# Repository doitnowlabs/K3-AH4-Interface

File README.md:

K3-AH4-Interface
================

A project that enables the use of the Icom AH4 autotuner with the Elecraft K3 and KX3 radios.

Edit -- March 2021: Greetings from the future! Many people have got in contact with me or my Dad asking for more information about this project over the ~7 years since it was created (if you contacted me and I didn't see the message/did not respond, I apologize!). Although it's a little late, I'm uploading all the files I have relating to the k3-ah4 interface so hopefully others can reproduce it without needing to rely on me checking my GitHub messages infrequently.

One note is that this project switches RS232 lines in and out of circuit with an analog switch, which definitely does not comply with the RS232 standard. The project worked great in the state I'm uploading it in, but it wouldn't pass a compliance test. As with all my work, use at your own risk, and have fun!

Schem. and board files are Eagle format. There's a free version of Eagle available to download if you don't own a copy already.

Ben

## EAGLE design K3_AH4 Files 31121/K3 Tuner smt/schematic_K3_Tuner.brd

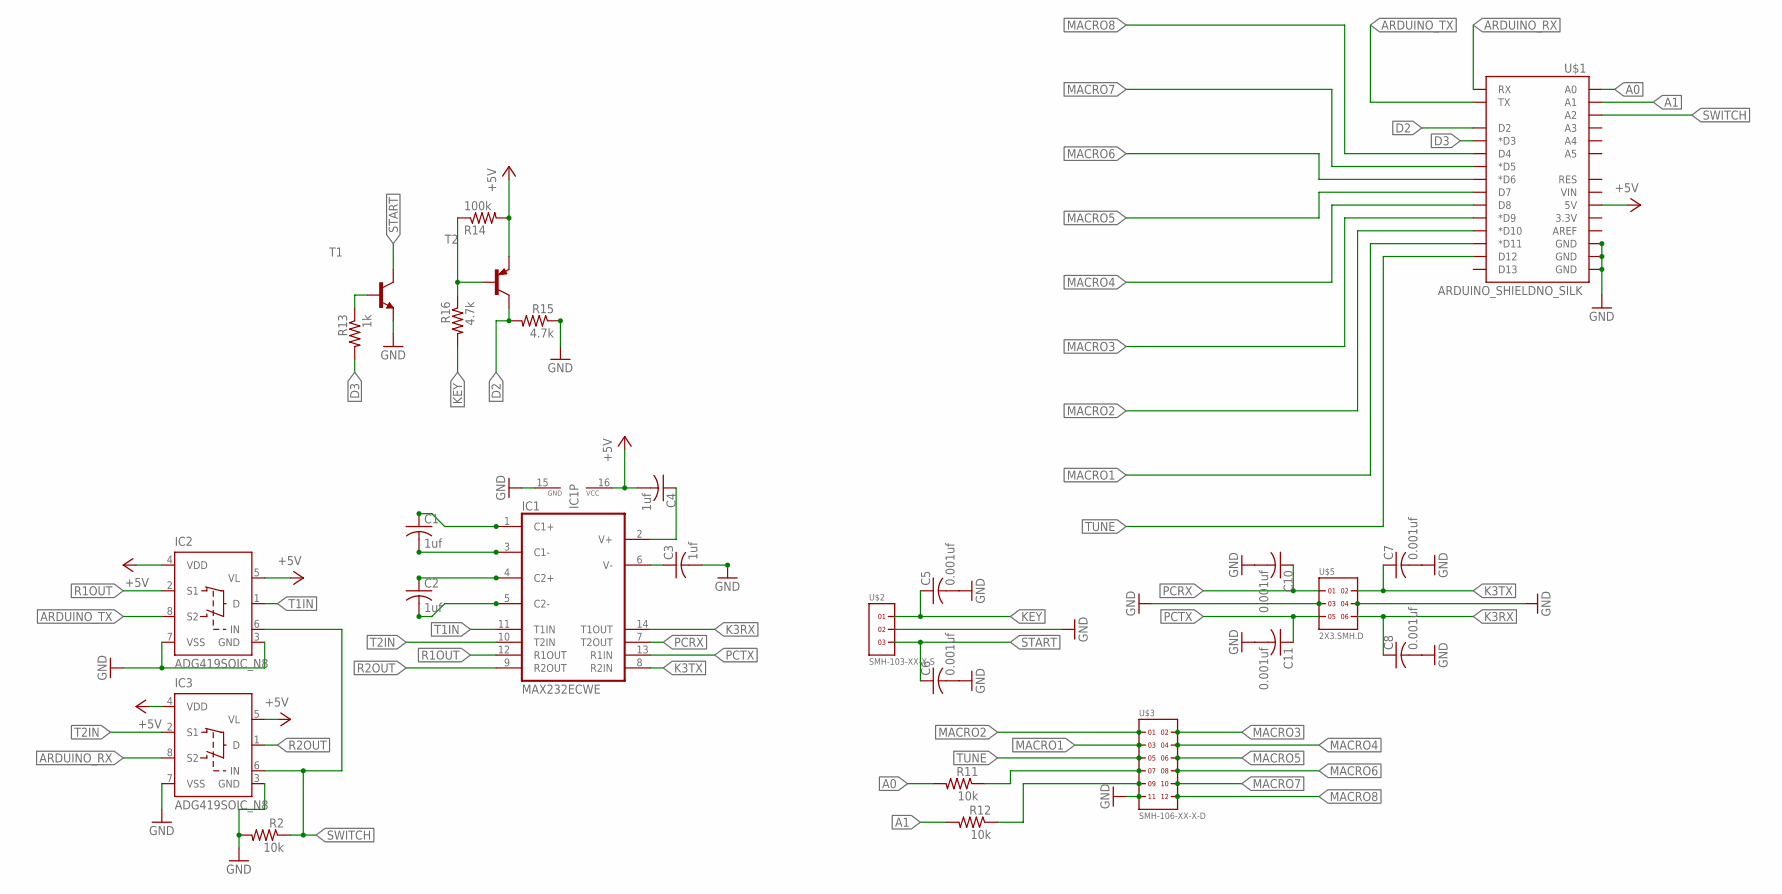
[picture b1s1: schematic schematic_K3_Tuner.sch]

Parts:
C1, C2, C3, C4: 1uf; C0805
C5, C6, C7, C8, C10, C11: 0.001uf; C0805
IC1: MAX232ECWE; SO16L
IC2, IC3: ADG419SOIC_N8; SOIC8
R2, R11, R12: 10k; M0805
R13: 1k; M0805
R14: 100k; M0805
R15, R16: 4.7k; M0805
T1: MMBT3904LT1-NPN-SOT23-BEC; SOT23-BEC
T2: MMBT3906LT1-PNP-SOT23-BEC; SOT23-BEC
U$1: ARDUINO_SHIELDNO_SILK; DUEMILANOVE_VIAS
U$2: SMH-103-XX-X-S
U$3: SMH-106-XX-X-D
U$5: 2X3.SMH.D; SMH-103-XX-X-D

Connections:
+5V: C4.2, IC1.16 (VCC), IC2.4 (VDD), IC2.5 (VL), IC3.4 (VDD), IC3.5 (VL), R14.2, T2.E, U$1.5V
A0: R11.2, U$1.A0
A1: R12.2, U$1.A1
ARDUINO_RX: IC3.8 (S2), U$1.RX
ARDUINO_TX: IC2.8 (S2), U$1.TX
D2: R15.2, T2.C, U$1.D2
D3: R13.2, U$1.D3 (*D3)
GND: C3.2, C5.2, C6.2, C7.2, C8.2, C10.2, C11.2, IC1.15 (GND), IC2.3 (GND), IC2.7 (VSS), IC3.3 (GND), IC3.7 (VSS), R2.2, R15.1, T1.E, U$1.GND@0 (GND), U$1.GND@1 (GND), U$1.GND@2 (GND), U$2.2, U$3.11, U$5.3, U$5.4
K3RX: C8.1, IC1.14 (T1OUT), U$5.6
K3TX: C7.1, IC1.8 (R2IN), U$5.2
KEY: C5.1, R16.2, U$2.1
MACRO1: U$1.D11 (*D11), U$3.3
MACRO2: U$1.D10 (*D10), U$3.1
MACRO3: U$1.D9 (*D9), U$3.2
MACRO4: U$1.D8, U$3.4
MACRO5: U$1.D7, U$3.6
MACRO6: U$1.D6 (*D6), U$3.8
MACRO7: U$1.D5 (*D5), U$3.10
MACRO8: U$1.D4, U$3.12
unnamed: R11.1, U$3.7
unnamed: R12.1, U$3.9
unnamed: C2.2, IC1.5 (C2-)
unnamed: C2.1, IC1.4 (C2+)
unnamed: C1.2, IC1.3 (C1-)
unnamed: C1.1, IC1.1 (C1+)
unnamed: C3.1, IC1.6 (V-)
unnamed: R13.1, T1.B
unnamed: R14.1, R16.1, T2.B
unnamed: C4.1, IC1.2 (V+)
PCRX: C10.1, IC1.7 (T2OUT), U$5.1
PCTX: C11.1, IC1.13 (R1IN), U$5.5
R1OUT: IC1.12 (R1OUT), IC2.2 (S1)
R2OUT: IC1.9 (R2OUT), IC3.1 (D)
START: C6.1, T1.C, U$2.3
SWITCH: IC2.6 (IN), IC3.6 (IN), R2.1, U$1.A2
T1IN: IC1.11 (T1IN), IC2.1 (D)
T2IN: IC1.10 (T2IN), IC3.2 (S1)
TUNE: U$1.D12, U$3.5

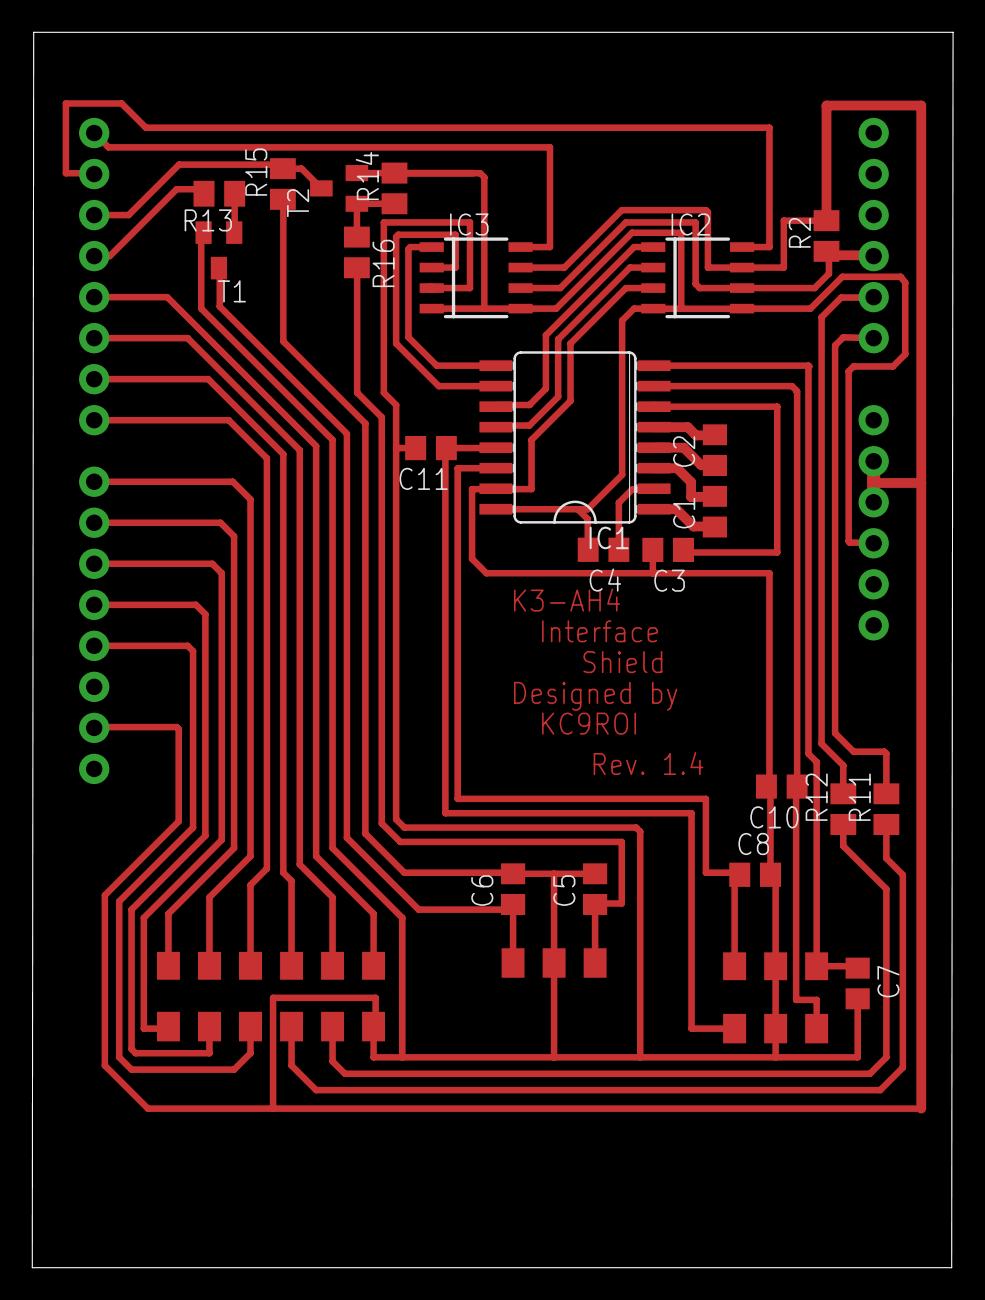
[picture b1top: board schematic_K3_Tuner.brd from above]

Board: 2 copper layers, 57.0 x 76.5 mm, 26 parts (0 on the bottom side), 38 nets.

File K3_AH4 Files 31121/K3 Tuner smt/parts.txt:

Partlist

Exported from schematic_K3_Tuner.sch at 3/28/2014 2:09:03 AM

EAGLE Version 6.5.0 Copyright (c) 1988-2013 CadSoft

Assembly variant: 

Part     Value                 Device                    Package          Library          Sheet

C1       1uf                   C-USC0805                 C0805            rcl              1
C2       1uf                   C-USC0805                 C0805            rcl              1
C3       1uf                   C-USC0805                 C0805            rcl              1
C4       1uf                   C-USC0805                 C0805            rcl              1
C5       0.001uf               C-USC0805                 C0805            rcl              1
C6       0.001uf               C-USC0805                 C0805            rcl              1
C7       0.001uf               C-USC0805                 C0805            rcl              1
C8       0.001uf               C-USC0805                 C0805            rcl              1
C10      0.001uf               C-USC0805                 C0805            rcl              1
C11      0.001uf               C-USC0805                 C0805            rcl              1
IC1      MAX232ECWE            MAX232ECWE                SO16L            maxim            1
IC2      ADG419SOIC_N8         ADG419SOIC_N8             SOIC8            K3Library        1
IC3      ADG419SOIC_N8         ADG419SOIC_N8             SOIC8            K3Library        1
R2       10k                   R-US_M0805                M0805            resistor         1
R11      10k                   R-US_M0805                M0805            resistor         1
R12      10k                   R-US_M0805                M0805            resistor         1
R13      1k                    R-US_M0805                M0805            resistor         1
R14      100k                  R-US_M0805                M0805            resistor         1
R15      4.7k                  R-US_M0805                M0805            resistor         1
R16      4.7k                  R-US_M0805                M0805            resistor         1
T1                             MMBT3904LT1-NPN-SOT23-BEC SOT23-BEC        transistor       1
T2                             MMBT3906LT1-PNP-SOT23-BEC SOT23-BEC        transistor       1
U$1      ARDUINO_SHIELDNO_SILK ARDUINO_SHIELDNO_SILK     DUEMILANOVE_VIAS SparkFun-Boards  1
U$2      SMH-103-XX-X-S        SMH-103-XX-X-S            SMH-103-XX-X-S   SAMTEC_Headers   1
U$3      SMH-106-XX-X-D        SMH-106-XX-X-D            SMH-106-XX-X-D   SAMTEC_Headers   1
U$5      2X3.SMH.D             2X3.SMH.D                 SMH-103-XX-X-D   samtec_Headers_2 1

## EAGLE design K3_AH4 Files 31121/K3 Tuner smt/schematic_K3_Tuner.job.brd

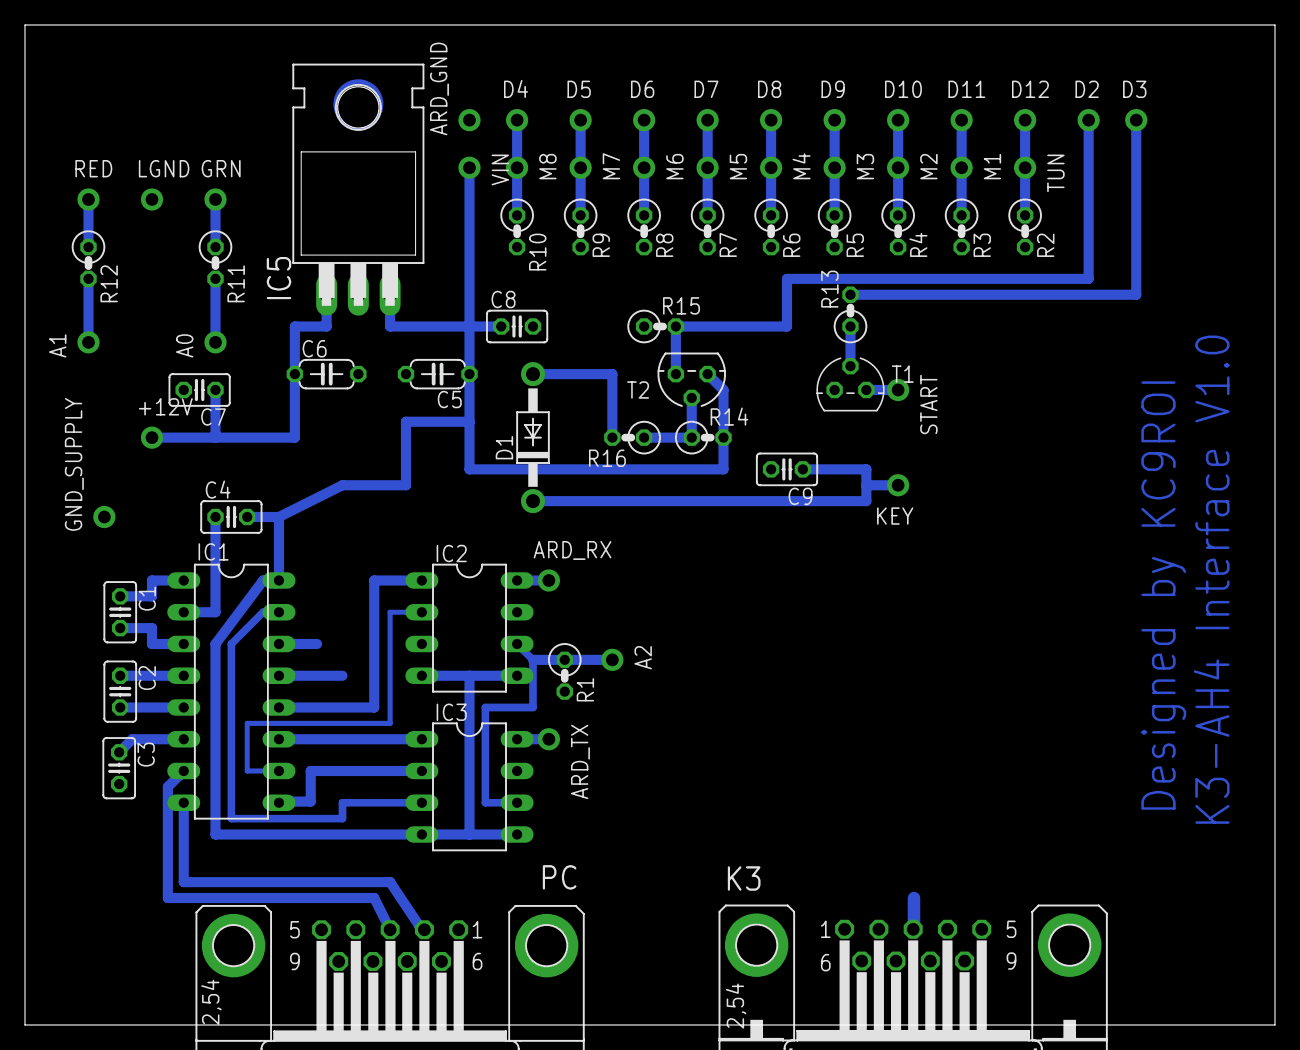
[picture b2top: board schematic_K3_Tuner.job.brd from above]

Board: 2 copper layers, 100.0 x 80.0 mm, 68 parts (0 on the bottom side), 40 nets.

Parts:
+12V: 1X01-CLEANBIG
A0, A1, A2: 1X01-CLEANBIG
ARD_GND: 1X01-CLEANBIG
ARD_RX: 1X01-CLEANBIG
ARD_TX: 1X01-CLEANBIG
C1, C2, C3, C4: 1uf; C025-025X050
C5, C6: 10uf; C050-024X044
C7, C8, C9: 0.003uf; C025-025X050
D1: 1N4004; DO41-10
D2, D3, D4, D5, D6, D7, D8, D9, D10, D11, D12: 1X01-CLEANBIG
GND_SUPPLY: 1X01-CLEANBIG
GRN: 1X01-CLEANBIG
IC1: MAX232; DIL16
IC2, IC3: ADG419; DIL08
IC5: 7805T; TO220H
K3: M09HP
KEY: 1X01-CLEANBIG
LGND: 1X01-CLEANBIG
M1, M2, M3, M4, M5, M6, M7, M8: 1X01-CLEANBIG
PC: F09HP
R1, R2, R3, R4, R5, R6, R7, R8, R9, R10, R11, R12: 10k; 0207/2V
R13: 1k; 0207/2V
R14: 100k; 0207/2V
R15, R16: 4.7k; 0207/2V
RED: 1X01-CLEANBIG
START: 1X01-CLEANBIG
T1: 2N3904; TO92
T2: 2N3906; TO92
TUN: 1X01-CLEANBIG
VIN: 1X01-CLEANBIG

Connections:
+5V: C4.2, C5.1, C8.1, IC1.16, IC2.4, IC2.5, IC3.4, IC3.5, IC5.3, R14.2, T2.3, VIN.1
+12V: +12V.1, C6.1, C7.1, IC5.1
ARDUINO_RX: ARD_RX.1, IC2.8
ARDUINO_TX: ARD_TX.1, IC3.8
GND: ARD_GND.1, C3.2, C5.2, C6.2, C7.2, C8.2, C9.2, GND_SUPPLY.1, IC1.15, IC2.3, IC2.7, IC3.3, IC3.7, IC5.2, K3.5, K3.G1, K3.G2, LGND.1, PC.5, PC.G1, PC.G2, R1.2, R2.2, R3.2, R4.2, R5.2, R6.2, R7.2, R8.2, R9.2, R10.2, R15.1, T1.3
K3RX: IC1.14, K3.3
K3TX: IC1.13, K3.2
MACRO1: D11.1, M1.1, R3.1
MACRO2: D10.1, M2.1, R4.1
MACRO3: D9.1, M3.1, R5.1
MACRO4: D8.1, M4.1, R6.1
MACRO5: D7.1, M5.1, R7.1
MACRO6: D6.1, M6.1, R8.1
MACRO7: D5.1, M7.1, R9.1
MACRO8: D4.1, M8.1, R10.1
unnamed: R12.1, RED.1
unnamed: GRN.1, R11.1
unnamed: C2.2, IC1.5
unnamed: C2.1, IC1.4
unnamed: A1.1, R12.2
unnamed: C1.2, IC1.3
unnamed: C1.1, IC1.1
unnamed: A0.1, R11.2
unnamed: C3.1, IC1.6
unnamed: IC1.10, IC2.2
unnamed: R13.1, T1.2
unnamed: IC1.12, IC2.1
unnamed: IC1.11, IC3.1
unnamed: START.1, T1.1
unnamed: D3.1, R13.2
unnamed: R14.1, R16.1, T2.2
unnamed: C4.1, IC1.2
unnamed: D2.1, R15.2, T2.1
unnamed: D1.A, R16.2
unnamed: C9.1, D1.C, KEY.1
PCRX: IC1.7, PC.3
PCTX: IC1.8, PC.2
SWITCH: A2.1, IC2.6, IC3.6, R1.1
T2IN: IC1.9, IC3.2
TUNE: D12.1, R2.1, TUN.1

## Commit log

2021-03-12 Uploaded Many Files
    Schematic, Board Layout, BOM, Code all included, all v. 1.4

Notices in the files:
parts and their libraries:
SparkFun-Boards: Licensing: Creative Commons ShareAlike 4.0 International - https://creativecommons.org/licenses/by-sa/4.0
